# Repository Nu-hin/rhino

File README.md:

# Rhino

## Description

Rhino is a robot based on AVR ATmega microcontroller.

Here's a list of its features:

* it runs on [AVR ATmega8](http://www.atmel.com/devices/atmega8.aspx "ATmega8") microcontroller;
* it moves around on cool tank tracks;
* it has 3 different sensors: ultrasonic distance sensor, lightning sensor, 3-axis accelerometer (as a removable module);
* it has a Bluetooth serial module (removable);
* it has 4 bright white LEDs to light its way;
* it has three general-purpose LED indicators (red, green, blue);
* it can produce an irritating sound;
* it has a potentiometer (to adjust continuous parameters) and a general-purpose button (to adjust discrete ones);
* it runs on 4 AA accumulators.

This repository contains PCB and firmware for Rhino. PCB files are prepared with [KiCAD](http://www.kicad-pcb.org/ "KiCAD").

Fork the repository and make your own Rhino!

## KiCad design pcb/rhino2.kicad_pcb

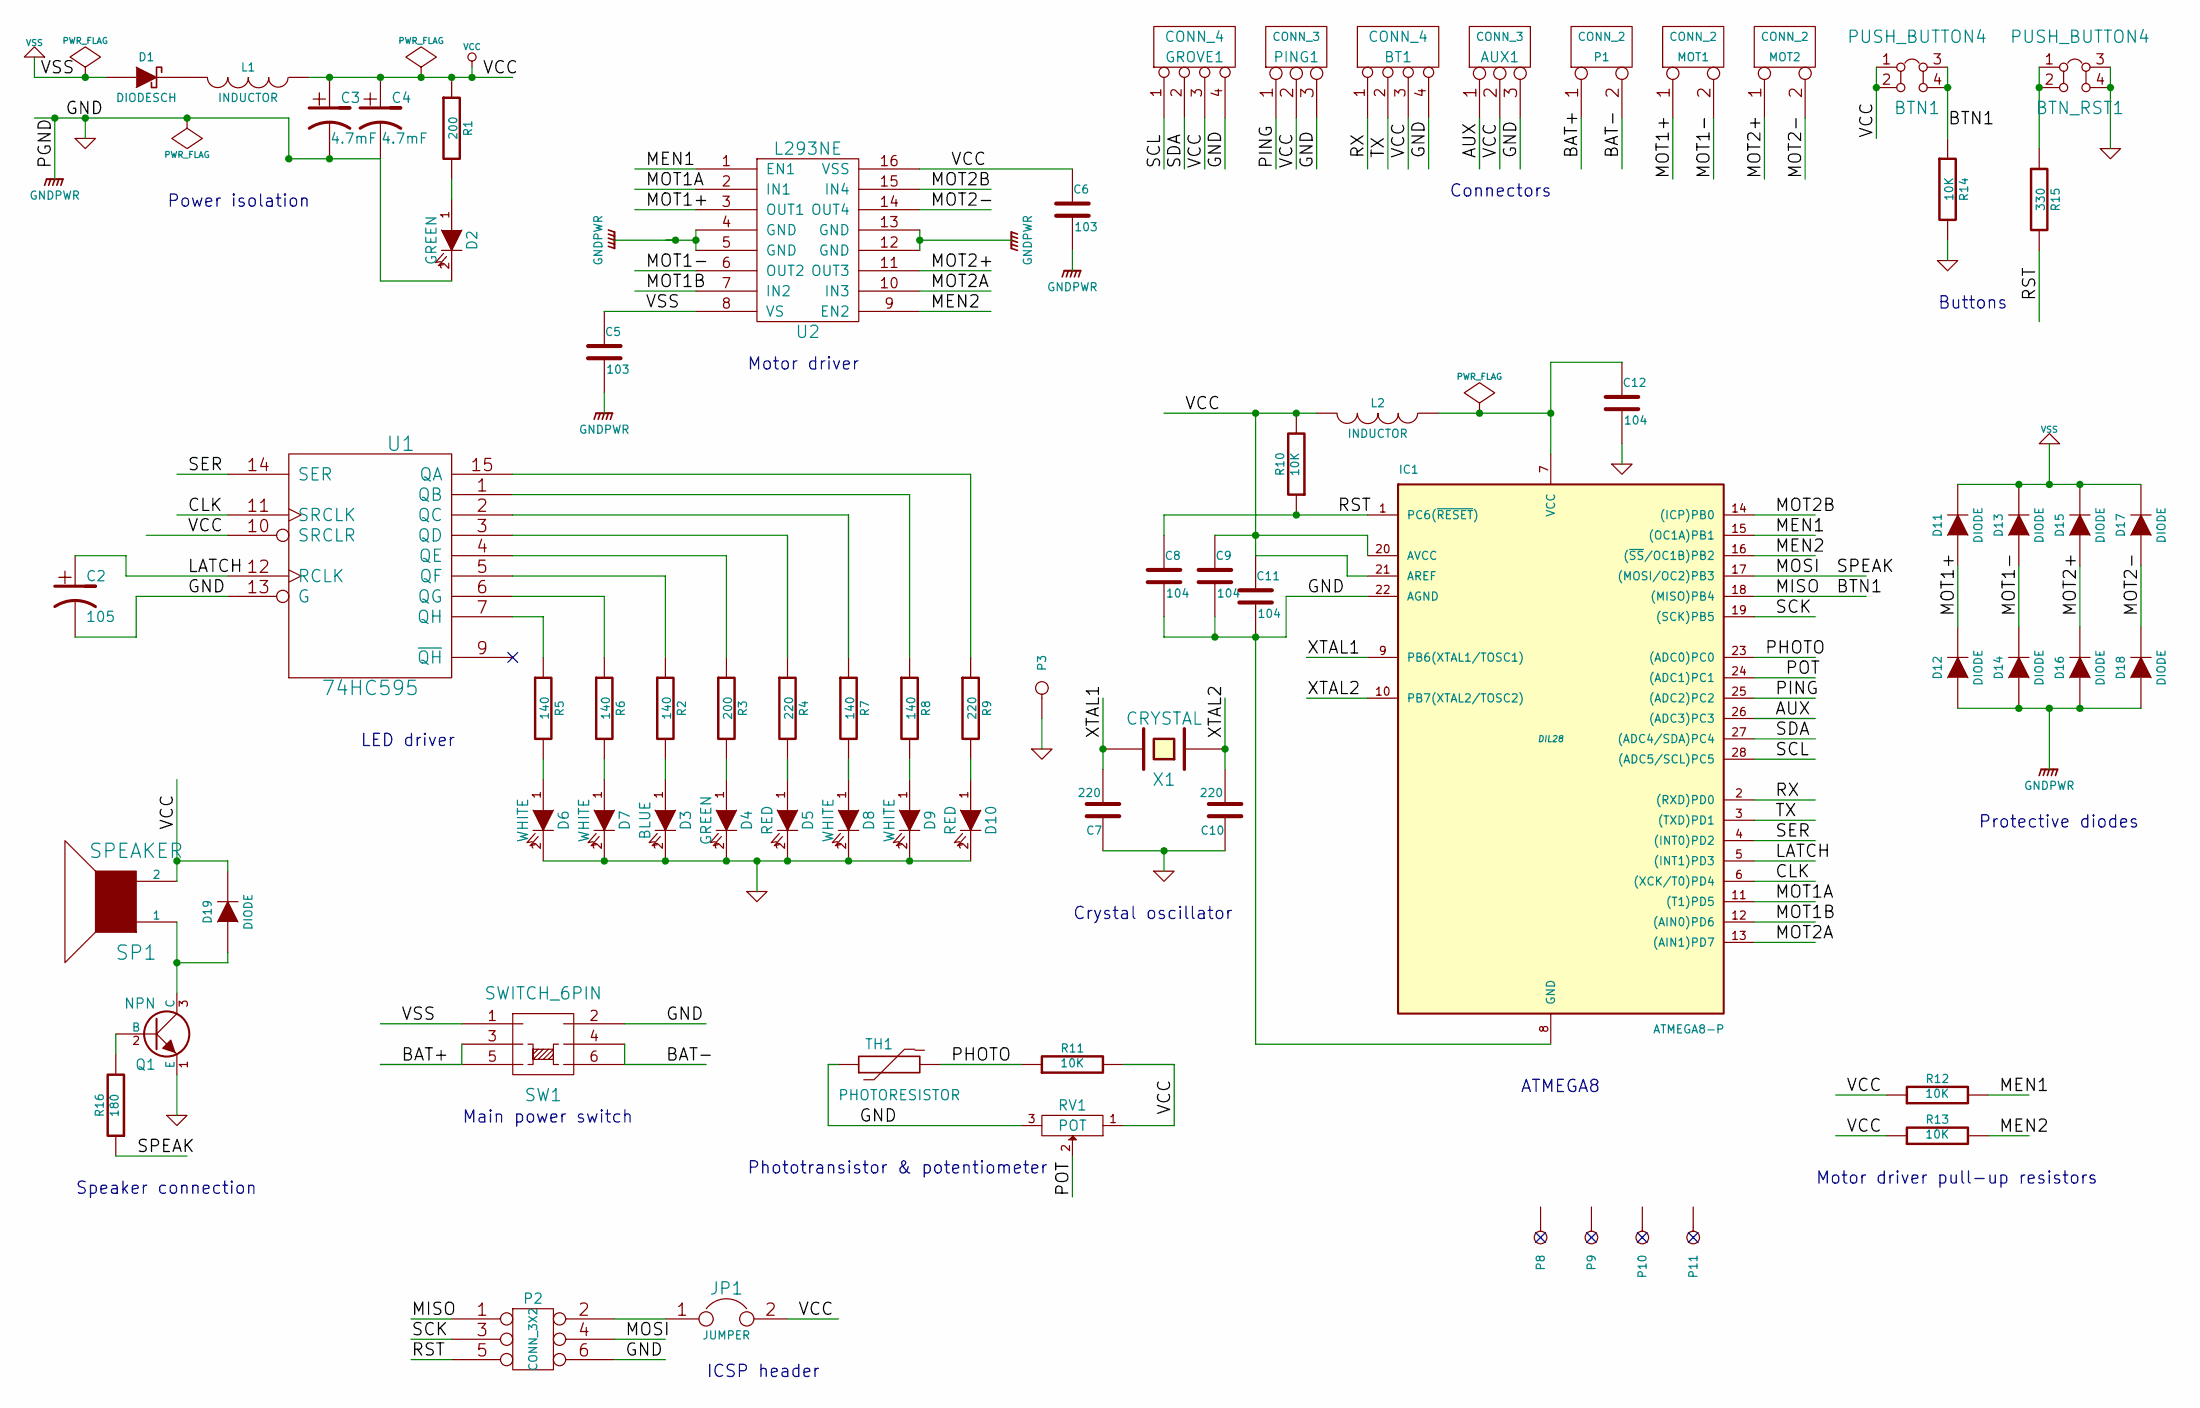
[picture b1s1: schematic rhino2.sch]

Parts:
AUX1: CONN_3
BT1: CONN_4
BTN1: PUSH_BUTTON4
BTN_RST1: PUSH_BUTTON4
C2: 105
C3, C4: 4.7mF
C5, C6: 103
C7, C10: 220
C8, C9, C11, C12: 104
D1: DIODESCH
D2, D4: GREEN
D3: BLUE
D5, D10: RED
D6, D7, D8, D9: WHITE
D11, D12, D13, D14, D15, D16, D17, D18, D19: DIODE
GROVE1: CONN_4
IC1: ATMEGA8-P; DIL28
JP1: JUMPER
L1, L2: INDUCTOR
MOT1, MOT2: CONN_2
P1: CONN_2
P2: CONN_3X2
P3, P8, P9, P10, P11: CONN_1
PING1: CONN_3
Q1: NPN
R1, R3: 200
R2, R5, R6, R7, R8: 140
R4, R9: 220
R10, R11, R12, R13, R14: 10K
R15: 330
R16: 180
RV1: POT
SP1: SPEAKER
SW1: SWITCH_6PIN
TH1: PHOTORESISTOR
U1: 74HC595
U2: L293NE
X1: CRYSTAL

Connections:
/AUX: AUX1.1, IC1.26 ((ADC3)PC3)
/BAT+: P1.1, SW1.3, SW1.5
/BAT-: P1.2 (PM), SW1.4, SW1.6
/BTN1: BTN1.3, BTN1.4, IC1.18 ((MISO)PB4), P2.1, R14.1
/CLK: IC1.6 ((XCK/T0)PD4), U1.11 (SRCLK)
/LATCH: C2.1, IC1.5 ((INT1)PD3), U1.12 (RCLK)
/MEN1: IC1.15 ((OC1A)PB1), R12.2, U2.1 (EN1)
/MEN2: IC1.16 ((~SS~/OC1B)PB2), R13.2, U2.9 (EN2)
/MOSI: IC1.17 ((MOSI/OC2)PB3), P2.4, R16.1
/MOT1+: D11.1 (A), D12.2 (K), MOT1.1, U2.3 (OUT1)
/MOT1-: D13.1 (A), D14.2 (K), MOT1.2 (PM), U2.6 (OUT2)
/MOT1A: IC1.11 ((T1)PD5), U2.2 (IN1)
/MOT1B: IC1.12 ((AIN0)PD6), U2.7 (IN2)
/MOT2+: D15.1 (A), D16.2 (K), MOT2.1, U2.11 (OUT3)
/MOT2-: D17.1 (A), D18.2 (K), MOT2.2 (PM), U2.14 (OUT4)
/MOT2A: IC1.13 ((AIN1)PD7), U2.10 (IN3)
/MOT2B: IC1.14 ((ICP)PB0), U2.15 (IN4)
/PHOTO: IC1.23 ((ADC0)PC0), R11.1, TH1.2
/PING: IC1.25 ((ADC2)PC2), PING1.1
/POT: IC1.24 ((ADC1)PC1), RV1.2
/RST: C8.1, IC1.1 (PC6(~RESET~)), P2.5, R10.1, R15.2
/RX: BT1.1, IC1.2 ((RXD)PD0)
/SCK: IC1.19 ((SCK)PB5), P2.3
/SCL: GROVE1.1, IC1.28 ((ADC5/SCL)PC5)
/SDA: GROVE1.2, IC1.27 ((ADC4/SDA)PC4)
/SER: IC1.4 ((INT0)PD2), U1.14 (SER)
/TX: BT1.2, IC1.3 ((TXD)PD1)
/XTAL1: C7.2, IC1.9 (PB6(XTAL1/TOSC1)), X1.2
/XTAL2: C10.2, IC1.10 (PB7(XTAL2/TOSC2)), X1.1
GND: AUX1.3, BT1.4, BTN_RST1.3, BTN_RST1.4, C2.2, C3.2, C4.2, C5.2, C6.2, C7.1, C8.2, C9.2, C10.1, C11.2, C12.2, D2.2 (K), D3.2 (K), D4.2 (K), D5.2 (K), D6.2 (K), D7.2 (K), D8.2 (K), D9.2 (K), D10.2 (K), D12.1 (A), D14.1 (A), D16.1 (A), D18.1 (A), GROVE1.4, IC1.8 (GND), IC1.22 (AGND), P2.6, P3.1, PING1.3, Q1.1 (E), R14.2, RV1.3, SW1.2, TH1.1, U1.8 (GND), U1.13 (G), U2.4 (GND), U2.5 (GND), U2.12 (GND), U2.13 (GND)
unnamed: JP1.1, P2.2
unnamed: D2.1 (A), R1.2
unnamed: R9.1, U1.15 (QA)
unnamed: D10.1 (A), R9.2
unnamed: D19.1 (A), Q1.3 (C), SP1.1
unnamed: Q1.2 (B), R16.2
unnamed: C12.1, IC1.7 (VCC), L2.1
unnamed: D3.1 (A), R2.2
unnamed: D4.1 (A), R3.2
unnamed: D5.1 (A), R4.2
unnamed: D6.1 (A), R5.2
unnamed: D7.1 (A), R6.2
unnamed: D8.1 (A), R7.2
unnamed: R3.1, U1.4 (QE)
unnamed: D9.1 (A), R8.2
unnamed: R5.1, U1.7 (QH)
unnamed: R6.1, U1.6 (QG)
unnamed: R2.1, U1.5 (QF)
unnamed: R4.1, U1.3 (QD)
unnamed: R7.1, U1.2 (QC)
unnamed: R8.1, U1.1 (QB)
unnamed: D1.2 (K), L1.2
unnamed: BTN_RST1.1, BTN_RST1.2, R15.1
VCC: AUX1.2 (PM), BT1.3, BTN1.1, BTN1.2, C3.1, C4.1, C6.1, C9.1, C11.1, D19.2 (K), GROVE1.3, IC1.20 (AVCC), IC1.21 (AREF), JP1.2, L1.1, L2.2, PING1.2 (PM), R1.1, R10.2, R11.2, R12.1, R13.1, RV1.1, SP1.2, U1.10 (SRCLR), U1.16 (VCC), U2.16 (VSS)
VSS: C5.1, D1.1 (A), D11.2 (K), D13.2 (K), D15.2 (K), D17.2 (K), SW1.1, U2.8 (VS)

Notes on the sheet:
Speaker connection
Main power switch
LED driver
Power isolation
Motor driver
ICSP header
Crystal oscillator
ATMEGA8
Phototransistor & potentiometer
Motor driver pull-up resistors
Buttons
Connectors
Protective diodes

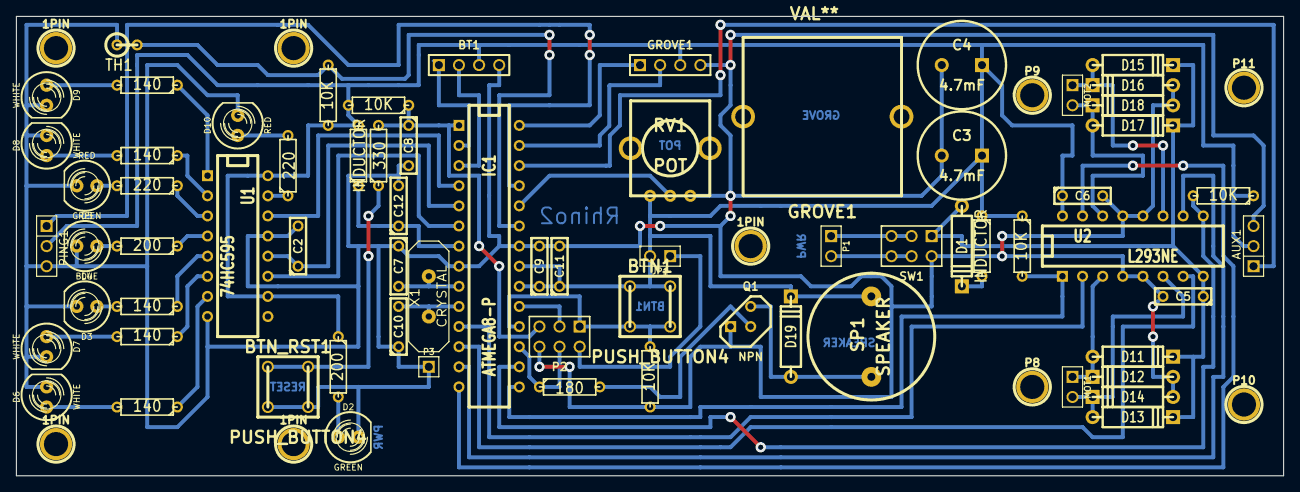
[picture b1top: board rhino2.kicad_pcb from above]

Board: 2 copper layers, 160.0 x 58.0 mm, 79 parts (0 on the bottom side), 55 nets.

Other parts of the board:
1PIN, 1PIN#2, 1PIN#3, 1PIN#4, 1PIN#5: P***; 1pin
GROVE1#2: VAL**; GROVE1

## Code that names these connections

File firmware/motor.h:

#ifndef MOTORH_H_
#define MOTORH_H_
#include "common.h"
#include <avr/io.h>

#define MOT1AD DDRD
#define MOT1BD DDRD
#define MOT2AD DDRD
#define MOT2BD DDRB
#define MOT1END DDRB
#define MOT2END DDRB


#define MOT1AP PORTD
#define MOT1BP PORTD
#define MOT2AP PORTD
#define MOT2BP PORTB
#define MOT1ENP PORTB
#define MOT2ENP PORTB

#define MOT1B (1<<PD5)
#define MOT1A (1<<PD6)
#define MOT2A (1<<PD7)
#define MOT2B (1<<PB0)
#define MOT1EN (1<<PB1)
#define MOT2EN (1<<PB2)


void initMotors();


void setMotorsAB(unsigned char m1a, unsigned char m1b,unsigned char m2a, unsigned char m2b);
void setMotors(int m1, int m2);

void enableMotors(unsigned char m1, unsigned char m2);

void forward();
void backward();
void left();
void right();
void stop();


#endif /* MOTORH_H_ */

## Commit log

2014-03-30 Create gh-pages branch via GitHub
2014-03-30 Fixed header.
2014-03-30 Embedded video
2014-03-30 Album images
2014-03-31 Gallery images thumbs
2014-03-31 Added result 800px thumbs
2014-03-31 Added image to README
2014-04-07 Dumped firmware and pcb files
2014-04-12 Modified makefile
2015-04-12 Changed programmer settings
